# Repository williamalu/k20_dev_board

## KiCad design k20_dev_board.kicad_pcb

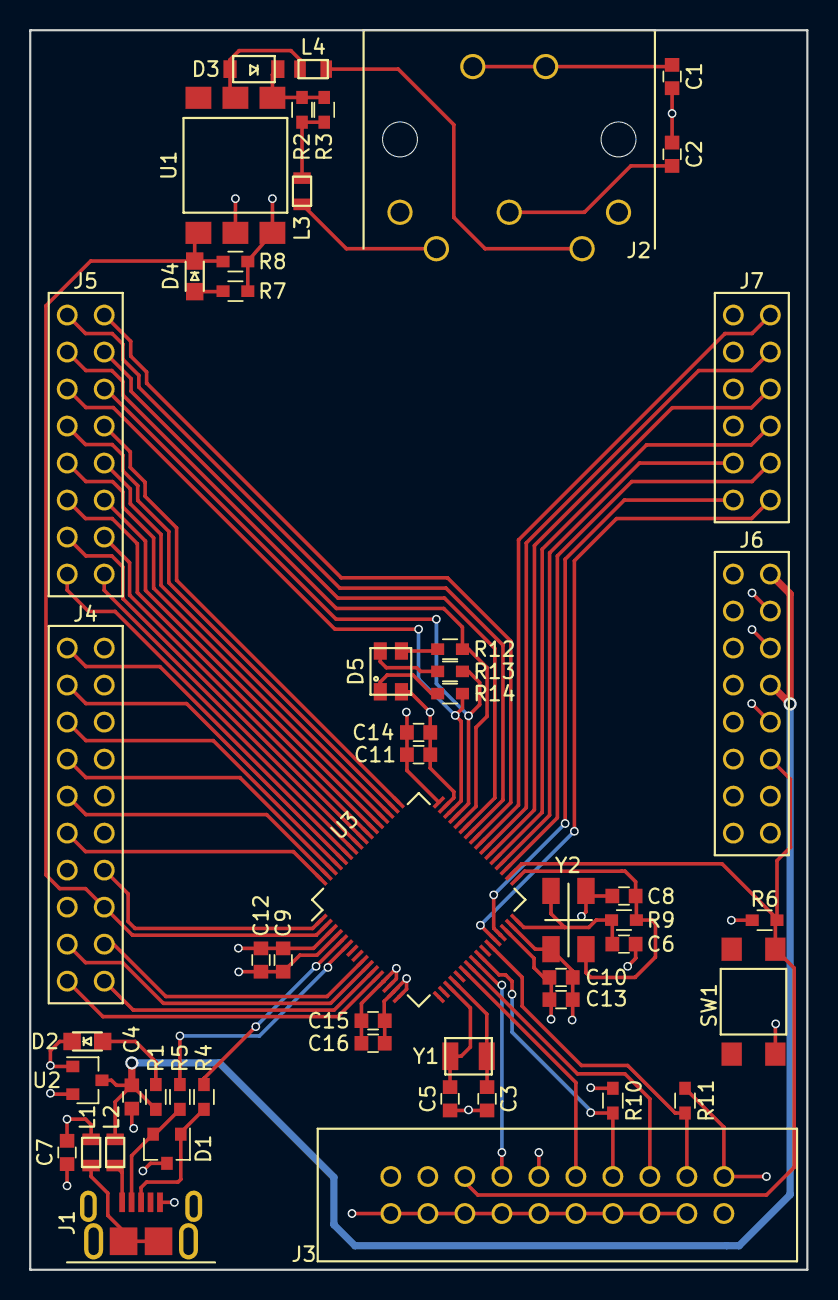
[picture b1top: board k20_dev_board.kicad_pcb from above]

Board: 4 copper layers, 53.3 x 85.1 mm, 52 parts (0 on the bottom side), 67 nets.

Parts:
C1, C2, C9, C10, C11, C15, C16: 0.1uF; C_0603
C3, C5, C6, C8: 22pF; C_0603
C4: 1.0uF; C_0603
C7: 10uF; C_0603
C12, C13, C14: 1uF; C_0603
D1: D_TVS_x2_AAC; SOT-23
D2, D4: LED; LTST-C170TGKT
D3: D; 1N4148W-TP
D5: LED_CRGB_altpin; XZM2CRKM2DGFBB45SCCB
J1: USB_OTG; 2040002-1
J2: MIDI-DIN-5; SDF-50J
J3: Conn_02x10_Odd_Even; SBH11-PBPC-D10-ST-BK
J4: Conn_02x10_Odd_Even; PPTC102LFBN-RC
J5, J6: Conn_02x08_Odd_Even; PPTC082LFBN-RC
J7: Conn_02x06_Odd_Even; PPTC062LFBN-RC
L1, L2: 330; MPZ2012S331AT000
L3, L4: 1k@100MHz; MMZ2012R102AT000
R1, R7: 1k; R_0603
R2: 806; R_0603
R3: 301; R_0603
R4, R5: 33; R_0603
R6: 10k; R_0603
R8: 200; R_0603
R9: 1M; R_0603
R10, R11: 100k; R_0603
R12, R13: 30.1; R_0603
R14: 127; R_0603
SW1: SW_Push; TL3305AF160QG
U1: H11L1; H11L1S(TA)
U2: MCP1702T-3302E/CB; SOT-23
U3: MK20DX128VLH5; LQFP-64_10x10mm_Pitch0.5mm
Y1: Crystal; ECS-.327-12.5-34B-TR
Y2: Crystal_GND24; ABM3B-8.000MHZ-B2-T

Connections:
+3V3: C7.2, C9.1, C10.1, C11.1, C12.1, C13.1, C14.1, C15.1, C16.1, J3.1, J4.16, J6.8, R6.1, R7.1, R8.1, R10.1, R11.1, U1.6, U2.2, U3.3, U3.13, U3.14, U3.30, U3.48
+5V: C4.2, J6.10, J6.16, L2.1, R1.2, U2.3
/ADC0_DM0: J4.18, U3.10
/ADC0_DM3: J4.20, U3.12
/ADC0_DP0: J4.17, U3.9
/ADC0_DP3: J4.19, U3.11
/JTAG_TCLK: J3.9, U3.22
/JTAG_TDI: J3.5, U3.23
/JTAG_TDO: J3.13, U3.24
/JTAG_TMS: J3.7, R10.2, U3.25
/PTA12/FTM1_CH0: J7.2, U3.28
/PTA13/FTM1_CH1: J7.1, U3.29
/PTB0/FTM1_CH0: J7.4, U3.35
/PTB1/FTM1_CH1: J7.3, U3.36
/PTB2: J7.6, U3.37
/PTB3: J7.8, U3.38
/PTB16: J7.10, U3.39
/PTB17: J7.12, U3.40
/PTB18: J5.1, U3.41
/PTB19: J5.2, U3.42
/PTC0: J5.3, U3.43
/PTC1/FTM0_CH0: J5.4, R12.1, U3.44
/PTC2/FTM0_CH1: J5.5, R13.1, U3.45
/PTC3/FTM0_CH2: J5.6, R14.1, U3.46
/PTC4/FTM0_CH3: J5.7, U3.49
/PTC5: J5.8, U3.50
/PTC6: J5.9, U3.51
/PTC7: J5.10, U3.52
/PTC8: J5.11, U3.53
/PTC9: J5.12, U3.54
/PTC10: J5.13, U3.55
/PTC11: J5.14, U3.56
/PTD0: J5.15, U3.57
/PTD1: J5.16, U3.58
/PTD2: J4.2, U3.59
/PTD3: J4.4, U3.60
/PTD4/FTM0_CH4: J4.6, U3.61
/PTD5/FTM0_CH5: J4.8, U3.62
/PTD6/FTM0_CH6: J4.10, U3.63
/PTD7/FTM0_CH7: J4.12, U3.64
/PTE0/UART1_TX: J4.13, U3.1
/PTE1/UART1_RX: D4.1, J4.15, R8.2, U1.4, U3.2
/~JTAG_TRST: J3.3, R11.2, U3.27
/~RESET: J3.15, J6.6, R6.2, SW1.2, U3.34
GND: C1.2, C2.2, C3.2, C4.1, C5.2, C6.2, C7.1, C8.2, C9.2, C10.2, C11.2, C12.2, C13.2, C14.2, C15.2, C16.2, D1.3, D2.1, D5.4, J1.5, J3.4, J3.6, J3.8, J3.10, J3.11, J3.12, J3.14, J3.16, J3.18, J3.20, J4.14, J6.12, J6.14, L1.2, SW1.1, U1.5, U2.1, U3.4, U3.15, U3.16, U3.31, U3.47, Y2.2, Y2.4
unnamed: C1.1, J2.~
unnamed: C2.1, J2.2
unnamed: C3.1, U3.20, Y1.1
unnamed: C5.1, U3.19, Y1.2
unnamed: C6.1, R9.2, U3.32, Y2.3
unnamed: C8.1, R9.1, U3.33, Y2.1
unnamed: D1.1, J1.3, R4.2
unnamed: D1.2, J1.2, R5.2
unnamed: D2.2, R1.1
unnamed: D3.1, R2.1, R3.1, U1.1
unnamed: D3.2, L4.1, U1.2
unnamed: D4.2, R7.2
unnamed: D5.1, R14.2
unnamed: D5.2, R13.2
unnamed: D5.3, R12.2
unnamed: J1.1, L2.2
unnamed: J1.6, L1.1
unnamed: J2.4, L3.2
unnamed: J2.5, L4.2
unnamed: L3.1, R2.2, R3.2
unnamed: R4.1, U3.5
unnamed: R5.1, U3.6

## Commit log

2017-09-25 created schematic for MK20DX128VLH5
2017-09-25 updated MK20DX128VLH5 schematic with better pin arrangement
2017-09-28 Franton's during class updates
2017-09-29 added unconnected crystals
2017-09-29 Added MIDI to UART
2017-10-02 moved MIDI schematic and replaced ferrite inductors with ferrite beads
2017-10-02 updated MIDI, added JTAG and bypass caps
2017-10-02 Added breakout pins, RGB LED, power LED, MIDI LED, and rearranged schematic
2017-10-02 Added megaohm resistor to crystal, generated netlist
2017-10-11 added footprints for all parts
2017-10-11 changed LED to common cathode
2017-10-12 converted to using external 3V3 reg, updated netlist, updated USB footprint to include pin 6 shield
2017-10-12 Fixed USB footprint
2017-10-12 Added edge line to MIDI connector footprint
2017-10-12 did a bunch of layout
2017-10-12 Reordered breakout pins to be manageable
2017-10-12 Finished adding traces to layout
2017-10-12 extended copper fills to match larger board size
